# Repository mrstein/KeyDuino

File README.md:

## KeyDuino Library

Welcome to KeyDuino official GitHub repository!  
Here you will find all the files you need to develop programs for your KeyDuino.  
You can also look at the [wiki](https://github.com/mrstein/KeyDuino/wiki) for informations about KeyDuino and its capabilities.  

The library is still under development, and everything is not perfect yet!  
That is why we would be very glad to hear from you about your experience with KeyDuino library ; if you encounter any problem, please feel free to open issues or contact us directly: that way we will be able to correct errors and improve the library.

### Tutorials & Projects
If you want to discover what you can do with your KeyDuino, join http://keyduino.forumsactifs.com/ !  
There you will find projects ideas, discussions, and tutorials, to help you get the best from your KeyDuino.  
If you have ideas to share, or questions to ask, don't hesitate! We would be very glad to hear from you.  

### Content
In this repository, you will find pretty much everything we develop for KeyDuino.

```
/---KeyDuino                  //The root folder of the repository  
|   +---library 		
|	|	+---NDEF              //The NDEF lib subfolder you need to put in your Arduino/libraries folder 
|   |	+---KeyDuino          //The KeyDuino lib subfolder you need to put in your Arduino/libraries folder  
|   |  	| +---examples        //All the examples supplied within the lib  
|   |   |   +---projects      //Examples associated with KeyDuino projects  
|   |   |   +---NDEF          //Examples using the NDEF lib   
|   |   |   +---...  
|   |   |  
|   |   +---...  
|   |
|   +---android_app           //The folder containing everything about Android application  
|   |   +---nfc_talker.apk    //The apk of the Android application we developped  
|   |    
|   +---hardware              //All hardware files of KeyDuino  
|   |   +---KeyDuino_board    //Hardware files for KeyDuino board  
|   |   +---antennas          //Hardware files for KeyDuino remote antenna  
```

### Compatibility
KeyDuino library is made to be used with [KeyDuino board](https://www.kickstarter.com/projects/1535978353/keyduino), but it also works by default with a classical Arduino Leonardo using a PN532 Shield, as long as communication is done through HSU.

### Contribution
KeyDuino library is based on Adafruit_NFCShield_I2C, with improvements by Seeed Studio, and HSU (High Speed Uart) driver added by Elechouse.

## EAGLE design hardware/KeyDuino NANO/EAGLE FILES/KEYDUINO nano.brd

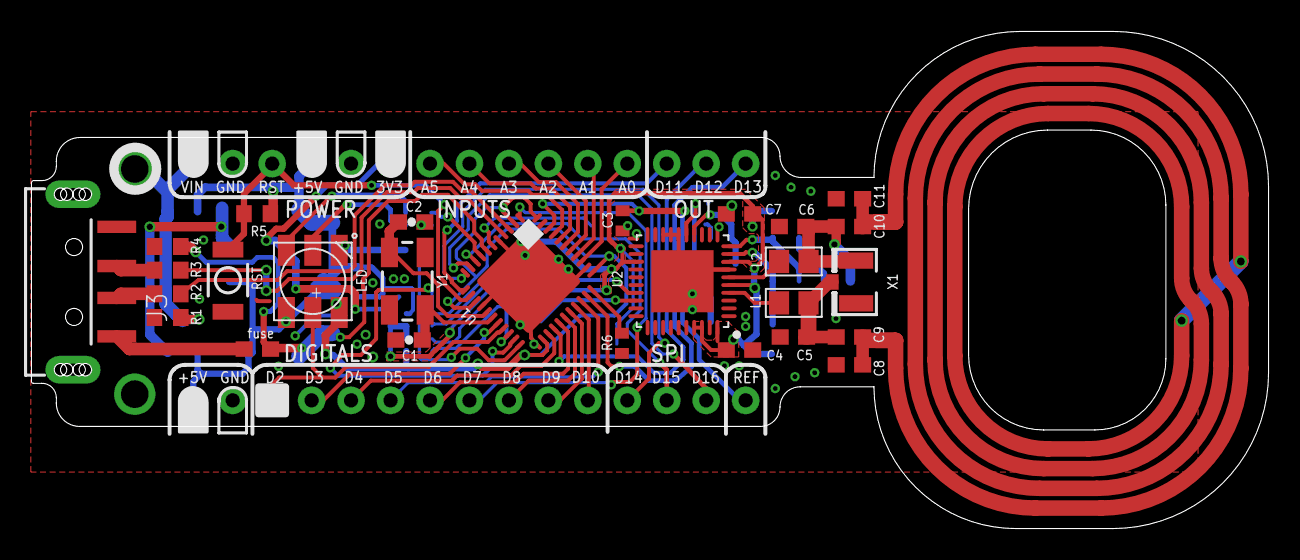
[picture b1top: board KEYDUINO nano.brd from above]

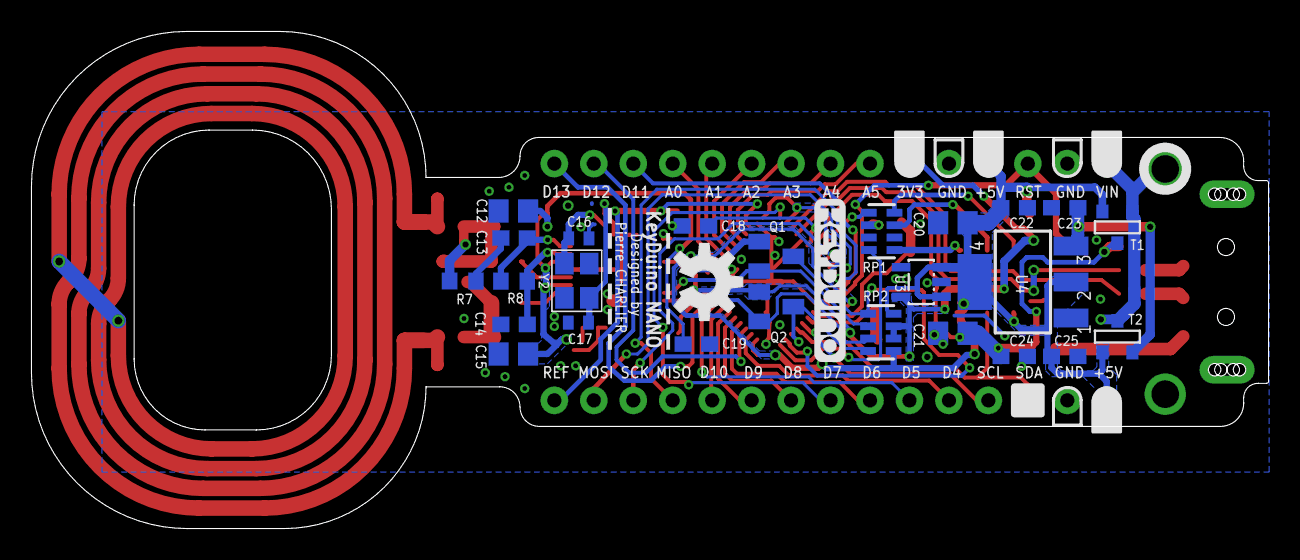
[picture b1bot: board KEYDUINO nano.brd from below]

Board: 2 copper layers, 79.6 x 32.0 mm, 58 parts (26 on the bottom side), 58 nets.

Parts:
C1, C2: 22pF; 0603-CAP
C3: 100nF; C0402
C4: 4.7uF; C0603
C5, C6: 220pF; C0603
C7, C14, C23, C24, C25: 100nF; C0603
C8, C11: 470pF; C0603
C9, C10: 180pF; C0603
C12, C15: 10uF; C0805
C13: 1nF; C0603
C16, C17: 18pF; C0402
C18, C19, C22: 1uF; C0603
C20, C21: 22uF; C0805
F1: fuse; 0603
H1, H2: SEW_HOLE-SMALL; SIMPLE_HOLE_SM
J1, J2: HEAD15-NOSS-1
J3: USBA-SMD-MALE-LOCKING; USB-A-SMT-MALE-LOCKING
L1, L2: 560nH; 0805@1
LED: RGBLED5050
LOGO1: OSHW-LOGOM; OSHW-LOGO-M
Q1, Q2: BSS138; SOT23
R1, R4, R5: 10K; R0603
R2, R3: 22; R0603
R6: 10K; R0402
R7: 2.7K; R0603
R8: 1.0K; R0603
RP1: 330; RES4NT
RP2: 10K; RES4NT
RST: RESET; 157SW
T1: FDN340P/PMV48XP; SOT-23
T2: PMV48XP; SOT-23
U1: ATMEGA32U4-XUMU; QFN44ML7X7
U2: PN532; HVQFN40-6X6
U3: LP2985-33DBVR; SOT23-DBV
U4: NCP1117-5; LINEAR_SOT223
U$1: KN1; KEYDUINO_NANO_ANTENNA
X1: U.FL
Y1: 16MHz; CRYSTAL-SMD-5X3
Y2: 27.12MHz; CRYSTAL_3.2X2.5

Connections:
+3V3: C4.2, C7.2, C12.2, C15.2, C19.1, J1.6, Q1.1, Q2.1, RP2.2, RP2.3, U2.5, U2.8, U2.23, U2.37, U2.38, U2.40, U3.5
+5V: C20.1, C22.1, C25.1, J1.4, J2.15, LED.1, LED.3, R5.1, RP2.1, RP2.4, T1.2, T2.3, U1.2, U1.14, U1.24, U1.34, U1.44, U3.1, U3.3, U4.2, U4.4
+VIN: C23.1, T2.2, U4.3
A0: J1.12, U1.36
A1: J1.11, U1.37
A2: J1.10, U1.38
A3: J1.9, U1.39
A4: J1.8, U1.40
A5: J1.7, U1.41
AREF: C3.1, J2.1, U1.42
CON1: C5.2, C9.1, L1.1, X1.3
D0/RX: Q2.3, RP2.8, U1.20
D1/TX: Q1.3, RP2.5, U1.21
D2: J2.13, LED.2, U1.19
D3: J2.12, U1.18
D4: J2.11, U1.25
D5: J2.10, U1.31
D6: J2.9, U1.27
D7: J2.8, U1.1
D8: J2.7, U1.28
D9: J2.6, U1.29
D10: J2.5, U1.30
D11: J1.13, U1.12
D12: J1.14, U1.26
D13: J1.15, U1.32
D14(MISO): J2.4, U1.11
D15(SCK): J2.3, U1.9
D16(MOSI): J2.2, U1.10
D_N: R2.2, U1.3
D_P: R3.2, U1.4
GND: C1.2, C2.2, C3.2, C4.1, C5.1, C6.2, C7.1, C8.1, C11.2, C12.1, C14.1, C15.1, C16.1, C17.1, C18.2, C19.2, C20.2, C21.2, C22.2, C23.2, C24.2, C25.2, H2.P$1, J1.2, J1.5, J2.14, J3.GND1, R1.1, R4.1, R6.2, RP1.6, RST.1, U1.5, U1.15, U1.23, U1.35, U1.43, U1.EXP, U2.1, U2.3, U2.7, U2.11, U2.16, U2.17, U2.18, U2.TP, U3.2, U4.1
HSU_RX/3.3V: Q1.2, RP2.6, U2.27
HSU_TX/3.3V: Q2.2, RP2.7, U2.28
HWB: R6.1, U1.33
unnamed: J3.D-1, R2.1
unnamed: C1.1, U1.17, Y1.1
unnamed: LED.5, RP1.3
unnamed: C2.1, U1.16, Y1.3
unnamed: J3.D+1, R3.1
unnamed: C13.1, R7.1
unnamed: L1.2, U2.4
unnamed: L2.2, U2.6
unnamed: F1.2, J3.VBUS1
unnamed: LED.6, RP1.4
unnamed: LED.4, RP1.1
unnamed: C16.2, U2.14, Y2.1
unnamed: C17.2, U2.15, Y2.2
unnamed: C14.2, R8.2, U2.9
unnamed: C13.2, R8.1, U2.10
RESET: J1.3, R5.2, RST.2, U1.13
RXLED: RP1.5, U1.8
TX1_ANTENNA: C8.2, C9.2, U$1.TX2
TX2_ANTENNA: C10.1, C11.1, U$1.TX1
TXLED: RP1.8, U1.22
UCAP: C18.1, U1.6
VIN: H1.P$1, J1.1, R1.2, T1.3, T2.1
VUSB: C21.1, C24.1, F1.1, R4.2, T1.1, U1.7
XX1: C6.1, C10.2, L2.1, R7.2, X1.2

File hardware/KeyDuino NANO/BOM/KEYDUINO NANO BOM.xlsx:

Part | Qty | Value | Device | Package | Description | REF
CAPACITOR
C3 | 1 | 100nF | C-EUC0402 | C0402 | Capacitor | capacitor 0402 100nF
C16, C17 | 2 | 18pF | C-EUC0402 | C0402 | Capacitor | capacitor 0402 18pF
C1, C2 | 2 | 22pF | C-EUC0603 | C0603 | Capacitor | capacitor 0603 22pF
C5, C6 | 2 | 220pF, 5% | C-EUC0603 | C0603 | Capacitor | capacitor 0603 220pF, 5%
C9, C10 | 2 | 180pF, 5% | C-EUC0603 | C0603 | Capacitor | capacitor 0603 180pF, 5%
C8, C11 | 2 | 470pF, 5% | C-EUC0603 | C0603 | Capacitor | capacitor 0603 470pF, 5%
C13 | 1 | 1nF | C-EUC0603 | C0603 | Capacitor | capacitor 0603 1nF
C7, 14, C23, C24, C25 | 5 | 100nF | C-EUC0603 | C0603 | Capacitor | capacitor 0603 100nF
C18, C19, C22 | 3 | 1uF | C-EUC0603 | C0603 | Capacitor | capacitor 0603 1uF
C4 | 1 | 4.7uF | C-EUC0603 | C0603 | Capacitor | capacitor 0603 4,7uF
C12, C15 | 2 | 10uF | C-EUC0805 | C0805 | Capacitor | capacitor 0805 10uF
C20, C21 | 2 | 22uF | C-EUC0805 | C0805 | Capacitor | capacitor 0805 22uF
RESISTOR
R6 | 1 | 10K | R-EU_R0402 | R0402 | resistor | RESISTOR 0402 10K
R2, R3 | 2 | 22 | R-EU_R0603 | R0603 | resistor | RESISTOR 0603 22
R8 | 1 | 1.0K | R-EU_R0603 | R0603 | resistor | RESISTOR 0603 1K
R7 | 1 | 2.7K | R-EU_R0603 | R0603 | resistor | RESISTOR 0603 2,7K
R1, R4, R5 | 3 | 10K | R-EU_R0603 | R0603 | resistor | RESISTOR 0603 10K
RP1 | 1 | 330 | RES4NT, 0402 | RES4NT | resistors | 4 Resistor Array 330
RP2 | 1 | 10K | RES4NT, 0402 | RES4NT | resistors | 4 Resistor Array 10K
COMPONENTS
L1, L2 | 2 | 560nH | INDUCTOR0805 | 0805@1 | Inductors | inductor 560nH 0805
F1 | 1 | fuse | PTC0603 | 603 | Resettable Fuse PTC | FUSE 0603 750mA
LED | 1 | RGBLED5050 | RGBLED5050 | RGBLED5050 | 5050 LED | ! Way
CRYSTAL
Y1 | 1 | 16MHz | CRYSTAL5X3 | CRYSTAL-SMD-5X3 | Crystals | 16MHz KX-7
Y2 | 1 | 27.12MHz | CRYSTALTHIN | CRYSTAL_3.2X2.5 | Crystals | 7B-27.120MAAJ-T
CONNECTOR
USB | 1 | USB male | USB male | USB male | USB Connectors
X1 | 1 |  | ANTENNA_U.FL | U.FL | U.FL Connector | u.FL
RST | 1 | RESET | PB157 | 157SW
J1, J2 | 1 | HEAD16-NOSS HEAD16-NOSS HEAD16-NOSS |  |  |  | Header male 1*16 2,54mm
IC
U1 | 1 | ATMEGA32U4-XUMU | ATMEGA32U4-XUMU | QFN44ML7X7 |  | ATMEGA32U4-XUAU
U4 | 1 | NCP1117-5 | LINEAR_MC33269ST | LINEAR_SOT223 | REGULATOR | NCP1117ST50T3G
U3 | 1 | LP2985-33DBVR | LP2985-XXDBVR33 | SOT23-DBV | REGULATOR | LP2985-33DBVR
U2 | 1 | PN532 | PN532 | HVQFN40-6X6 | PN532 | PN532
MOSFET
T1 | 1 | FDN340P/PMV48XP | PMOSSOT23 | SOT-23 | MOS FET | FDN340P
T2 | 1 | PMV48XP | PMOSSOT23 | SOT-23 | MOS FET | PMV48XP
Q1, Q2 | 2 | BSS138 | MOSFET-NREFLOW | SOT23 | N-Channel Mosfet | BSS138

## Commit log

2017-12-15 EAGLE files changed
2017-12-15 add information
2018-02-10 Add KeyDuino NANO files
2018-02-21 ADD mifare identification
2018-03-14 Add read_detailed
2018-06-09 Added SW files
2018-06-09 Added debug
2018-06-13 Fixed bug in DMSG
2018-11-11 Add examples

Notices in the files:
parts and their libraries:
SparkFun-Connectors: Licensing: Creative Commons ShareAlike 4.0 International - https://creativecommons.org/licenses/by-sa/4.0
